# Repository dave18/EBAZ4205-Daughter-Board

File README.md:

# EBAZ4205-Daughter-Board
Simple daughter board for EBAZ4205 FPGA with VGA, PS2 and standard 2.54 header

Daughter board to add VGA, SD Card Breakout and PS2 {keyboard, not playstation ;-)}  functionality to the EBAZ54205 miner board.

Also brings out IO pins to standard 2.54 header for easier interfacing.  SD Card and PS2 signal also available on pin header.

All through hole for easy assembly

Notes:

PS2 needs 5v so a 12v needs to be taken to the 12v header +connector which feeds the 5v regulator, or a separate 5v source taken directly to the 5v header.
I've adapted my EBAZ4205 board to provide 3.3V out on the VCC pins on Data 1 and Data 2.  To do this I removed the diodes at D21 and D23 and run a wire from the 3.3V VCC pin of the serial interface at J7.  There are diodes on the daughter board to avoid accidental back powering of the EBAZ4205 board.  Without this mod VGA still works but an alternative way of powering the 3.3v circuit for the SD Card and PS2 3.3v side is needed.

Design could be improved by bringing the 2mm headers neader the edge of the board but they still connect fine as they are

The 2 individual 16 pin 2.54 headers could be changed to a proper 2 x 16 pin header (they are currently spaced slightly too far apart for a 2x16 IDC connector)

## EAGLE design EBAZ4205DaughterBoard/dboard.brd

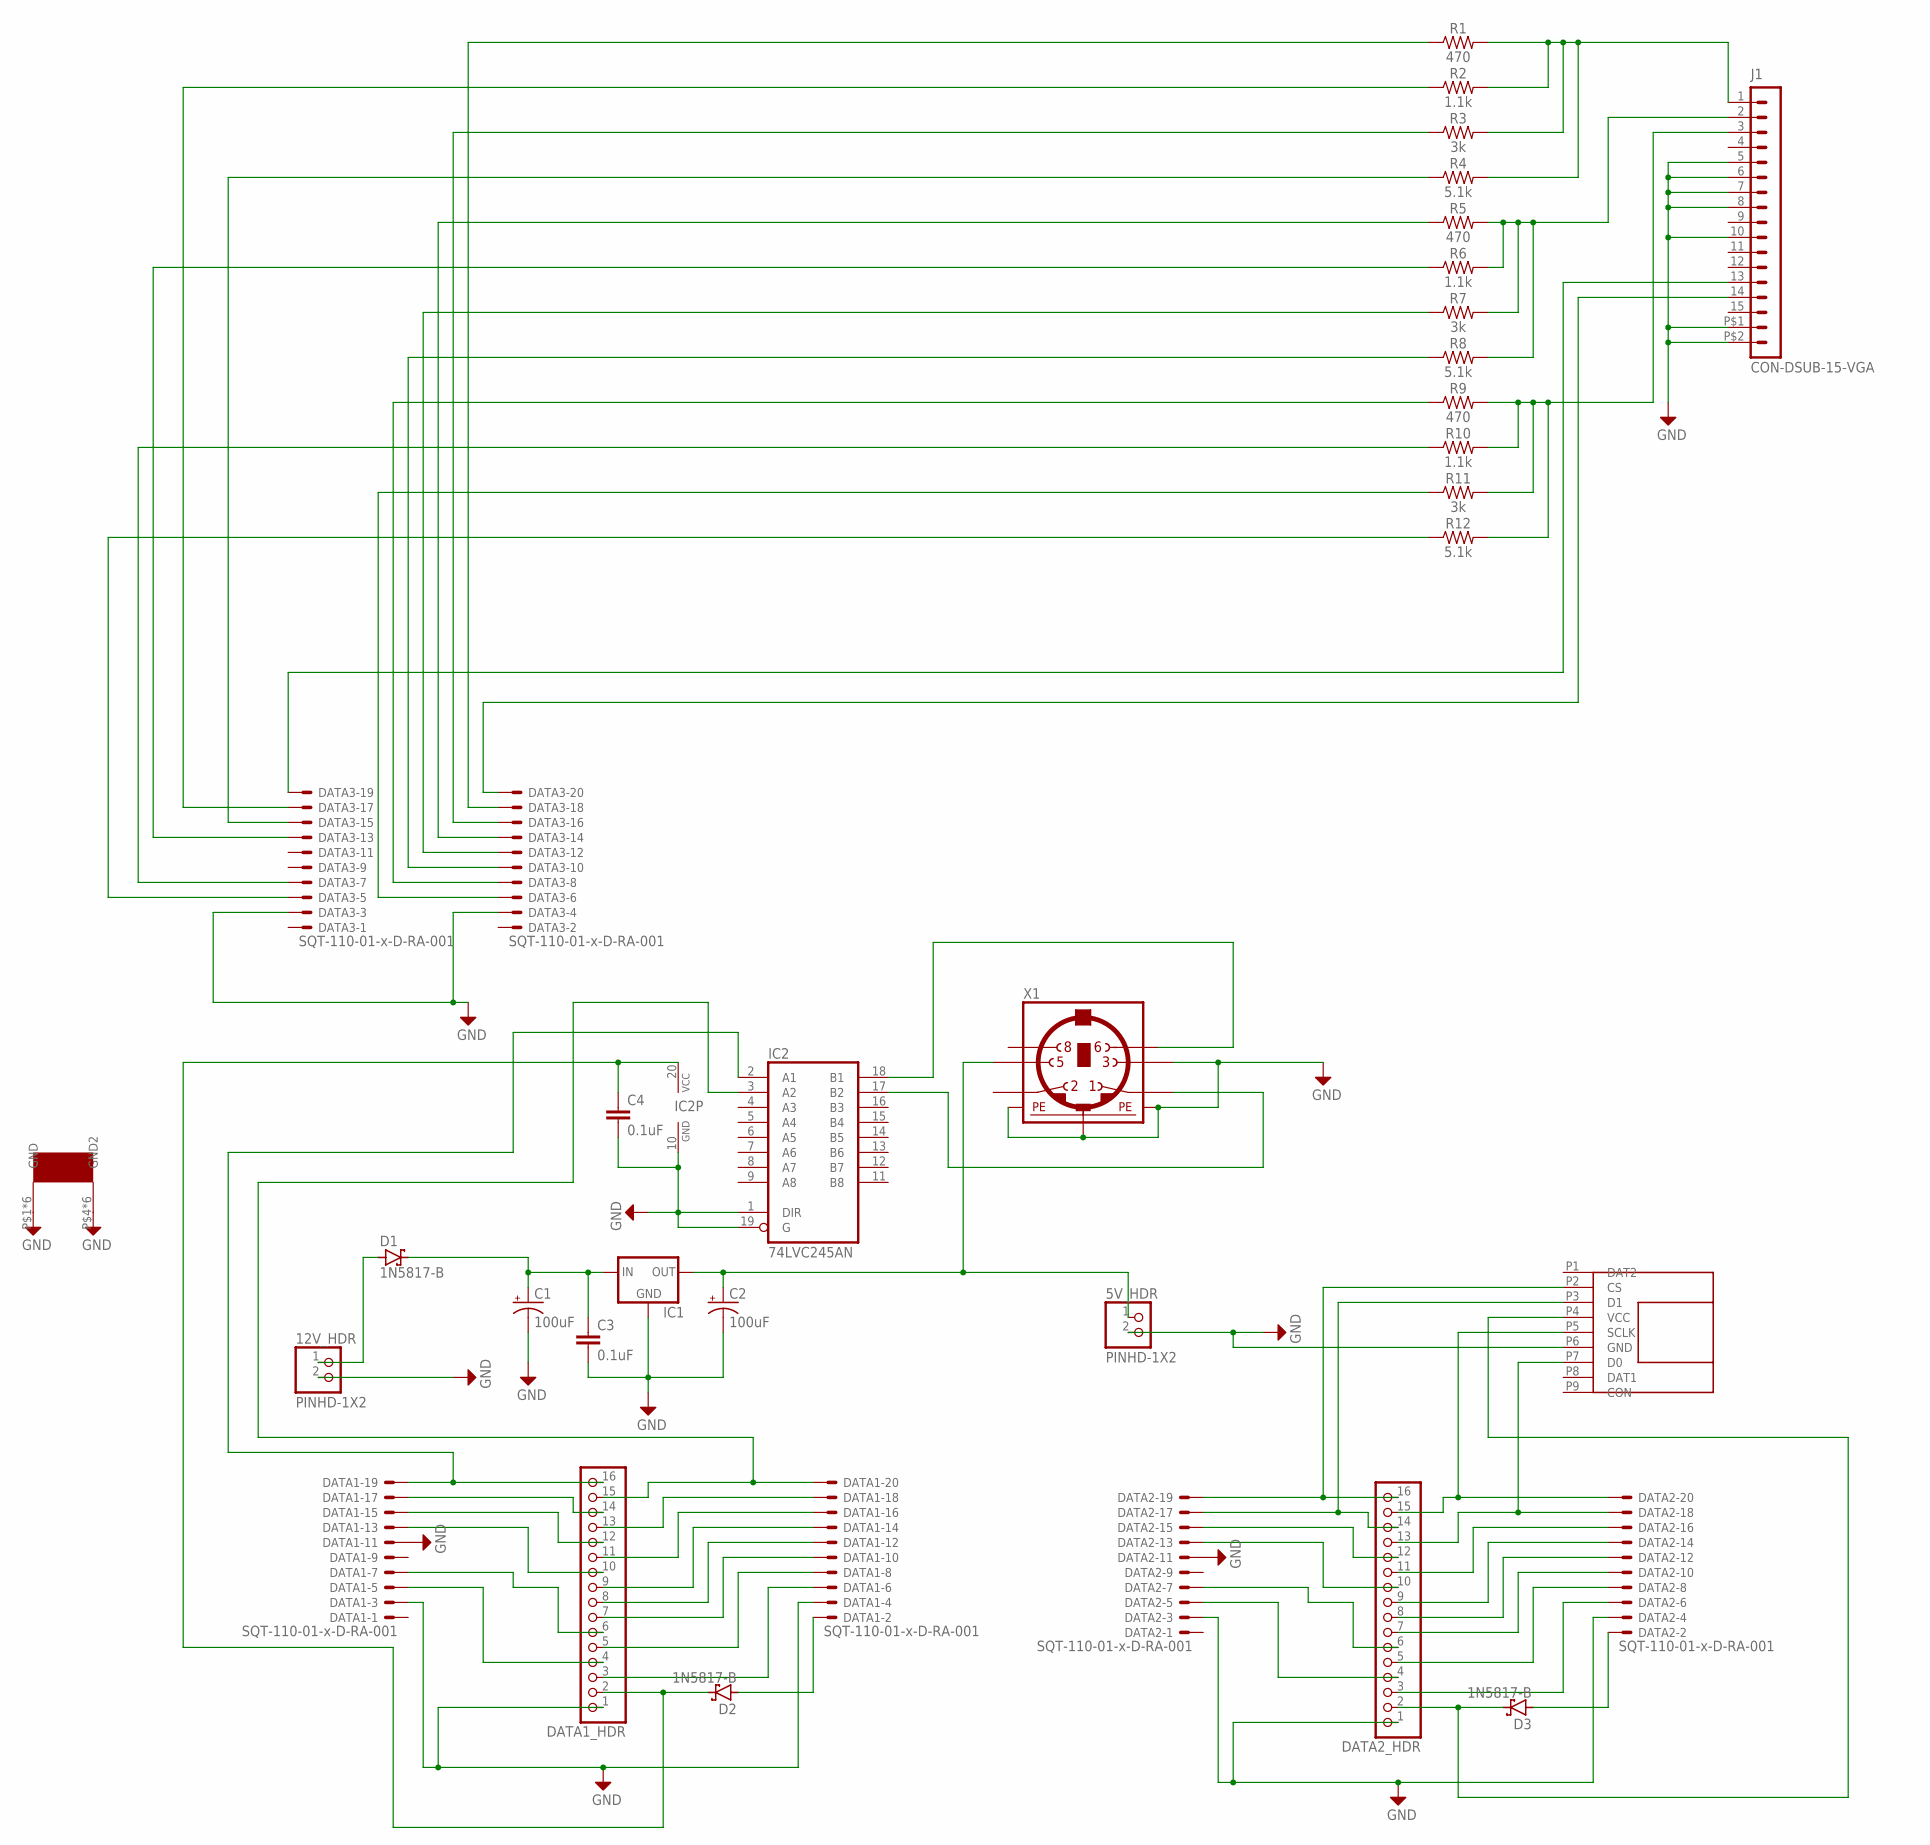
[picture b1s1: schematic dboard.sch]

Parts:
5V_HDR, 12V_HDR: PINHD-1X2; 1X02
C1, C2: 100uF; CPOL-RADIAL-2.5MM-6.5MM
C3, C4: 0.1uF; CAP-PTH-SMALL-KIT
D1, D2, D3: 1N5817-B; DO41-7.6
DATA1, DATA2, DATA3: SQT-110-01-x-D-RA-001; 332-20
DATA1_HDR, DATA2_HDR: PINHD-1X16; 1X16
IC1: 78XXL
IC2: 74LVC245AN; DIL20
J1: CON-DSUB-15-VGA; 181-015-212-171
R1, R5, R9: 470; AXIAL-0.3
R2, R6, R10: 1.1k; AXIAL-0.3
R3, R7, R11: 3k; AXIAL-0.3
R4, R8, R12: 5.1k; AXIAL-0.3
U$1: 7085THERMALPAD; 7805THERMALPAD
U$2: TF_CARD_BREAKOUT; OPEN-SMARTTFCARDBREAKOUT
X1: MINI_DIN_6; M_DIN6

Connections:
A20: DATA1.6, DATA1_HDR.3
B19: DATA1.8, DATA1_HDR.5
B20: DATA1.7, DATA1_HDR.6
C20: DATA1.10, DATA1_HDR.7
D18: DATA1.13, DATA1_HDR.10
D19: DATA1.15, DATA1_HDR.12
D20: DATA1.14, DATA1_HDR.9
DATA1_33V: D2.A, DATA1.2
DATA2_33V: D3.A, DATA2.2
E19: DATA1.17, DATA1_HDR.14
F19: DATA1.20, DATA1_HDR.15, IC2.3 (A2)
F20: DATA1.18, DATA1_HDR.13
G19: DATA2.8, DATA2_HDR.5
G20: DATA2.6, DATA2_HDR.3
GND: 5V_HDR.2, 12V_HDR.2, C1.2 (-), C2.2 (-), C3.2, C4.2, DATA1.3, DATA1.4, DATA1.11, DATA1_HDR.1, DATA2.3, DATA2.4, DATA2.11, DATA2_HDR.1, DATA3.3, DATA3.4, IC1.GND, IC2.1 (DIR), IC2.10 (GND), IC2.19 (G), J1.5, J1.6, J1.7, J1.8, J1.10, J1.P$1 (16), J1.P$2 (17), U$1.P$1 (GND), U$1.P$4 (GND2), U$1.P$6 (GND), U$1.P$7 (GND), U$1.P$8 (GND), U$1.P$9 (GND), U$1.P$10 (GND), U$1.P$11 (GND2), U$1.P$14 (GND2), U$1.P$19 (GND2), U$1.P$21 (GND2), U$1.P$24 (GND2), U$2.P6 (GND), X1.3, X1.SH1 (PE1), X1.SH2 (PE2), X1.SH3 (PE3)
H16: DATA1.5, DATA1_HDR.4
H17: DATA1.12, DATA1_HDR.8
H18: DATA1.16, DATA1_HDR.11
H20: DATA2.7, DATA2_HDR.6
HSYNC: DATA3.19, J1.13
J18: DATA2.5, DATA2_HDR.4
J19: DATA2.10, DATA2_HDR.7
J20: DATA2.13, DATA2_HDR.10
K17: DATA1.19, DATA1_HDR.16, IC2.2 (A1)
K18: DATA2.12, DATA2_HDR.8
K19: DATA2.14, DATA2_HDR.9
KBD_VCC: C4.1, D2.C, DATA1_HDR.2, IC2.20 (VCC)
L16: DATA2.16, DATA2_HDR.11
L19: DATA2.15, DATA2_HDR.12
unnamed: C1.1 (+), C3.1, D1.C, IC1.IN
PS2_CLK: IC2.18 (B1), X1.6
PS2_DATA: IC2.17 (B2), X1.1
SD_CS: DATA2.19, DATA2_HDR.16, U$2.P2 (CS)
SD_MISO: DATA2.18, DATA2_HDR.13, U$2.P7 (D0)
SD_MOSI: DATA2.17, DATA2_HDR.14, U$2.P3 (D1)
SD_SCLK: DATA2.20, DATA2_HDR.15, U$2.P5 (SCLK)
SD_VCC: D3.C, DATA2_HDR.2, U$2.P4 (VCC)
VCC+5V: 5V_HDR.1, C2.1 (+), IC1.OUT, X1.5
VGA_B0: DATA3.5, R12.P$1 (1)
VGA_B1: DATA3.6, R11.P$1 (1)
VGA_B2: DATA3.7, R10.P$1 (1)
VGA_B3: DATA3.8, R9.P$1 (1)
VGA_BLUE: J1.3, R9.P$2 (2), R10.P$2 (2), R11.P$2 (2), R12.P$2 (2)
VGA_G0: DATA3.10, R8.P$1 (1)
VGA_G1: DATA3.12, R7.P$1 (1)
VGA_G2: DATA3.13, R6.P$1 (1)
VGA_G3: DATA3.14, R5.P$1 (1)
VGA_GREEN: J1.2, R5.P$2 (2), R6.P$2 (2), R7.P$2 (2), R8.P$2 (2)
VGA_R0: DATA3.15, R4.P$1 (1)
VGA_R1: DATA3.16, R3.P$1 (1)
VGA_R2: DATA3.17, R2.P$1 (1)
VGA_R3: DATA3.18, R1.P$1 (1)
VGA_RED: J1.1, R1.P$2 (2), R2.P$2 (2), R3.P$2 (2), R4.P$2 (2)
VIN_12V: 12V_HDR.1, D1.A
VSYNC: DATA3.20, J1.14

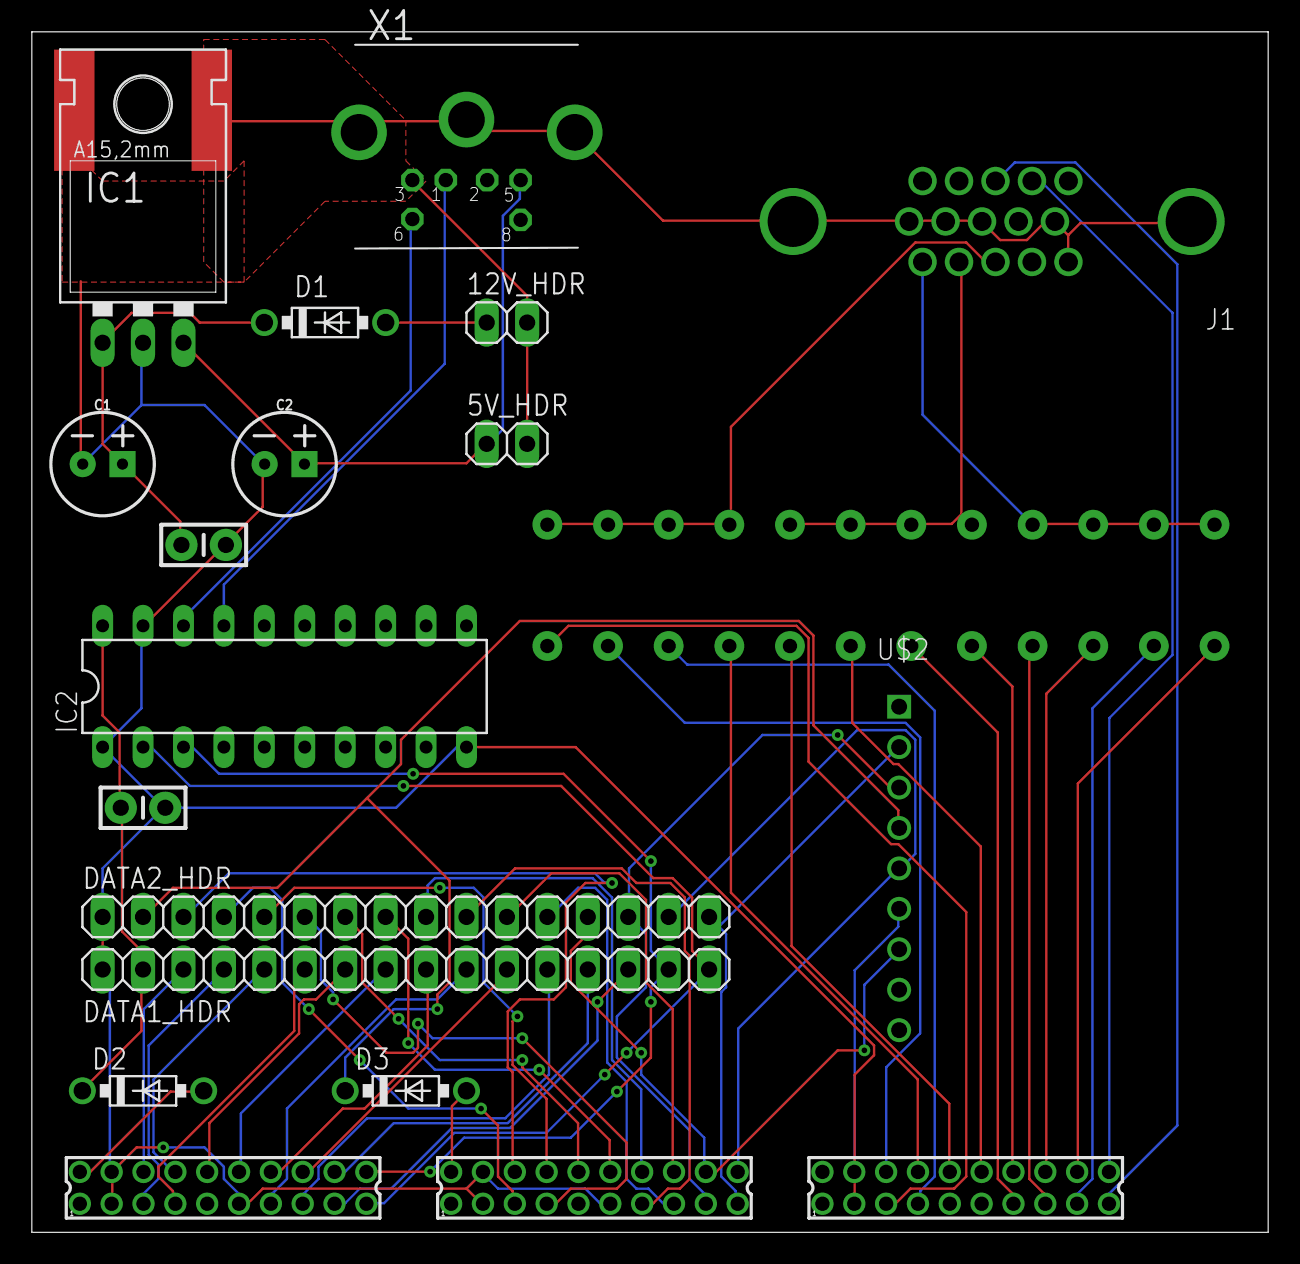
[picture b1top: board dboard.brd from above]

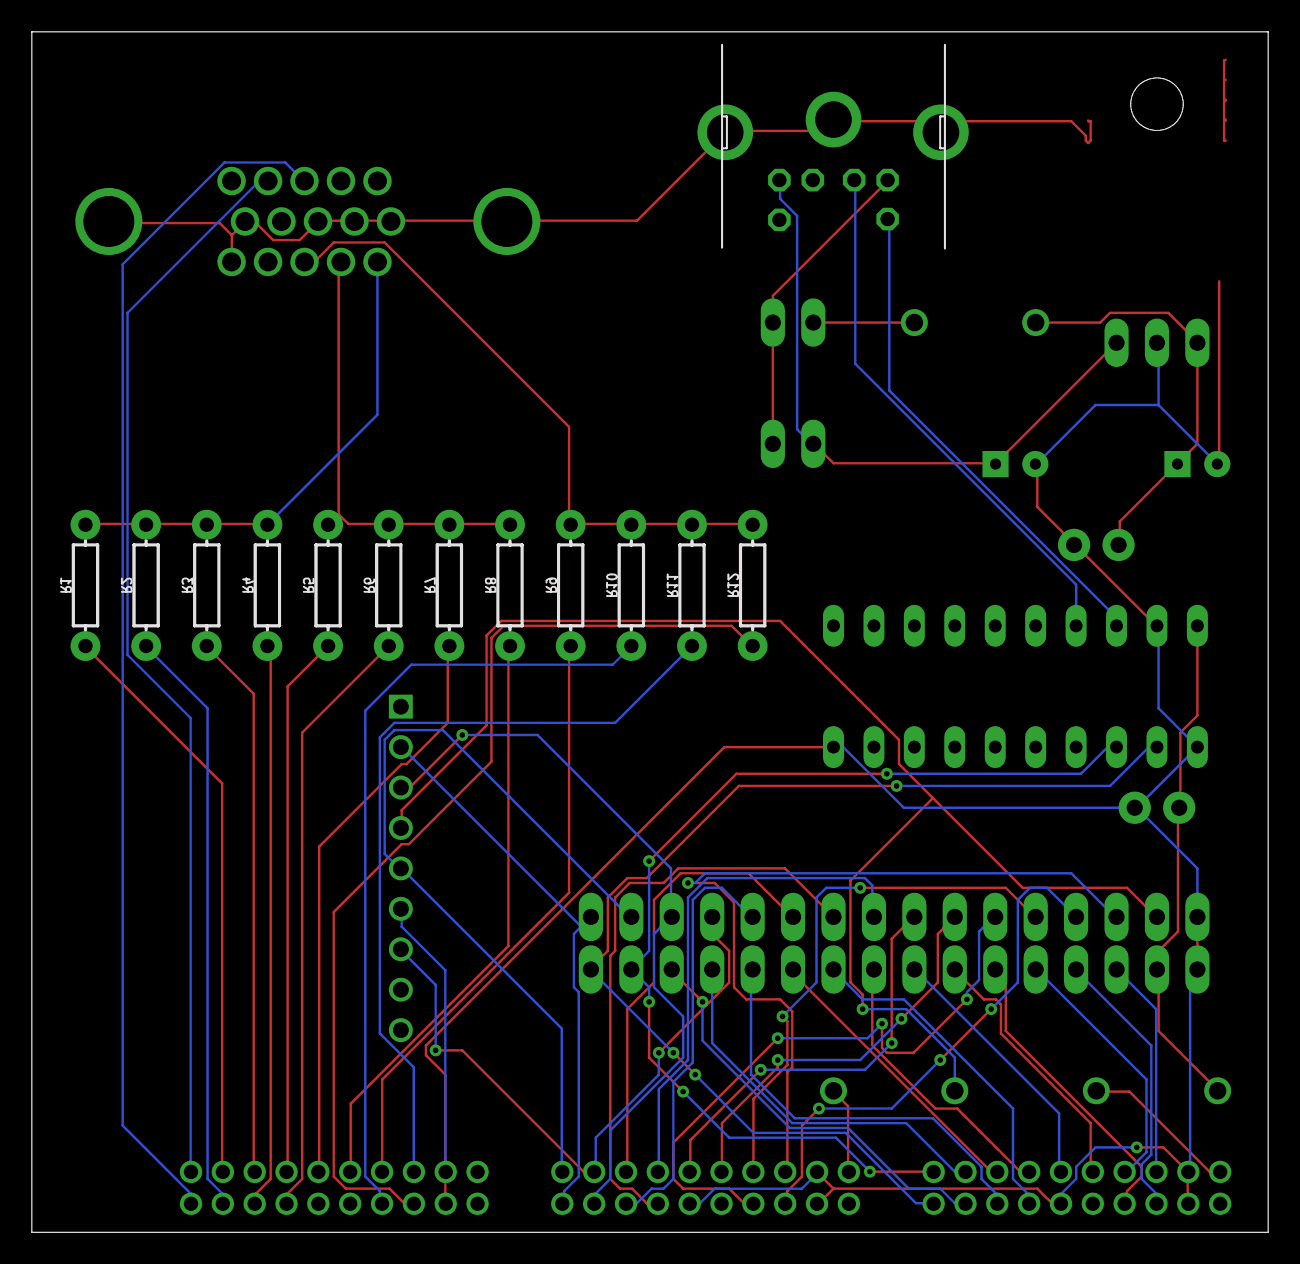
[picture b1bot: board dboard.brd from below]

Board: 2 copper layers, 77.7 x 75.4 mm, 32 parts (12 on the bottom side), 55 nets.

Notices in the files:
parts and their libraries:
m-pad-2.1: License : GNU General Public License version 2 (see bottom)
SparkFun-Resistors: Licensing: Creative Commons ShareAlike 4.0 International - https://creativecommons.org/licenses/by-sa/4.0
